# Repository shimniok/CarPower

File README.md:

CarPower
========

Automotive grade 5V power supply. Design to handle automotive electrical system spikes, wide temperature ranges.

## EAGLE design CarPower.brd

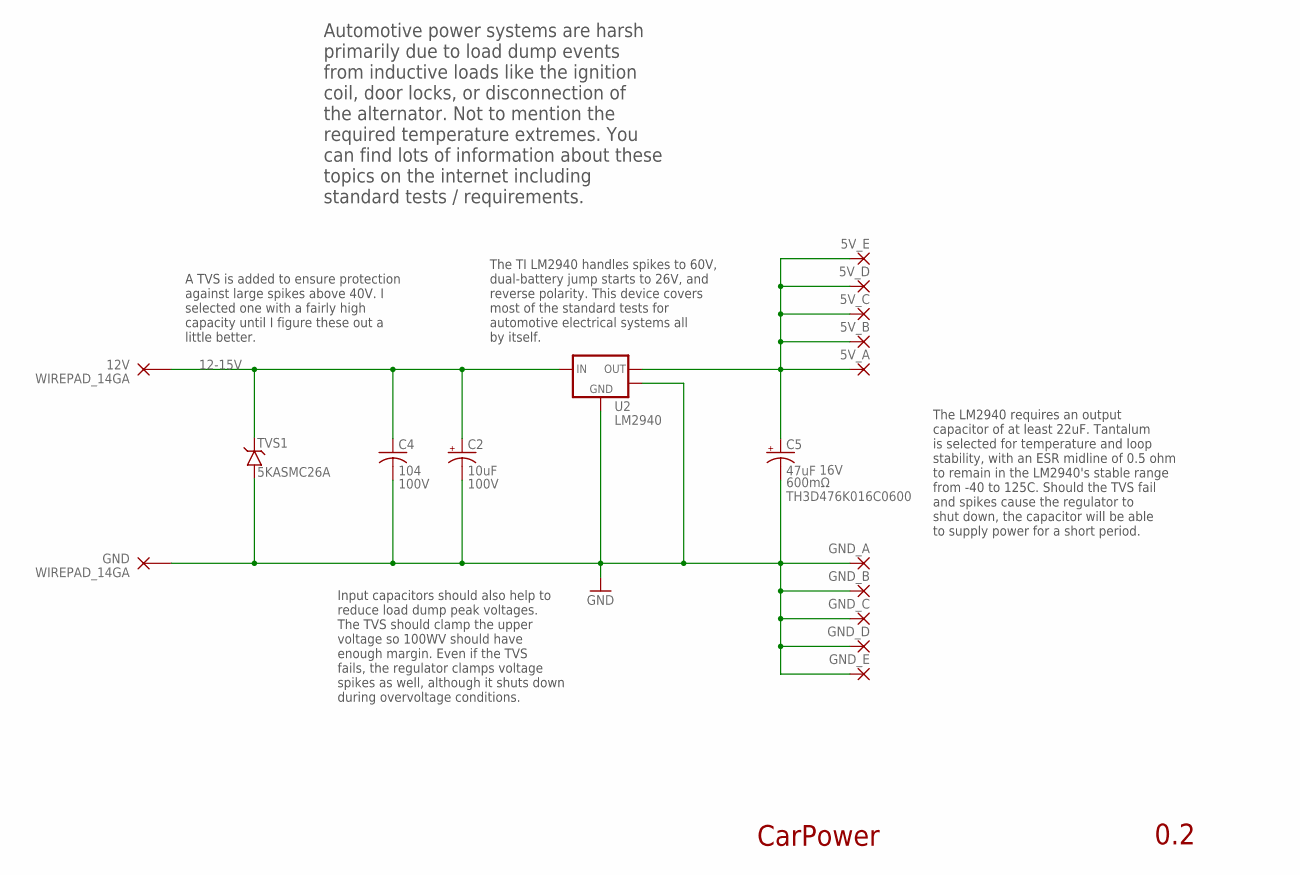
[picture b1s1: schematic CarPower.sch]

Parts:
5V_A, 5V_B, 5V_C, 5V_D, 5V_E: 1,6/0,9
12V: WIREPAD_14GA; PAD_14GA
C2: 10uF; E3,5-8; VOLTAGE 100V
C4: 104; C025-024X044; VOLTAGE 100V
C5: 47uF; SMC_C; VOLTAGE 16V; PARTNO TH3D476K016C0600
GND: WIREPAD_14GA; PAD_14GA
GND_A: 1,6/0,9
GND_B: 1,6/0,9
GND_C: 1,6/0,9
GND_D: 1,6/0,9
GND_E: 1,6/0,9
TVS1: 5KASMC26A; DO-214AB
U2: LM2940; TO263-3

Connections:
5V: 5V_A.1, 5V_B.1, 5V_C.1, 5V_D.1, 5V_E.1, C5.+, U2.3 (VOUT)
12-15V: 12V.P$1, C2.+, C4.1, TVS1.C, U2.1 (VIN)
GND: C2.-, C4.2, C5.-, GND.P$1, GND_A.1, GND_B.1, GND_C.1, GND_D.1, GND_E.1, TVS1.A, U2.2 (GND), U2.4 (TAB)

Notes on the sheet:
The TI LM2940 handles spikes to 60V, dual-battery jump starts to 26V, and reverse polarity. This device covers most of the standard tests for automotive electrical systems all by itself.
CarPower
0.2
A TVS is added to ensure protection against large spikes above 40V. I selected one with a fairly high capacity until I figure these out a little better.
The LM2940 requires an output capacitor of at least 22uF. Tantalum is selected for temperature and loop stability, with an ESR midline of 0.5 ohm to remain in the LM2940's stable range from -40 to 125C. Should the TVS fail and spikes cause the regulator to shut down, the capacitor will be able to s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
Automotive power systems are harsh primarily due to load dump events from inductive loads like the ignition coil, door locks, or disconnection of the alternator. Not to mention the required temperature extremes. You can find lots of information about these topics on the internet including standard 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
Input capacitors should also help to reduce load dump peak voltages. The TVS should clamp the upper voltage so 100WV should have enough margin. Even if the TVS fails, the regulator clamps voltage spikes as well, although it shuts down during overvoltage conditions.

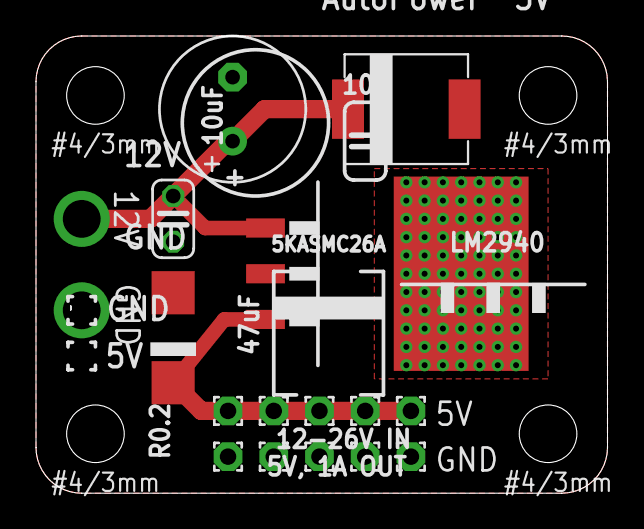
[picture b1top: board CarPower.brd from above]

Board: 2 copper layers, 31.8 x 25.4 mm, 21 parts (0 on the bottom side), 3 nets.

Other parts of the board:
U$1, U$2, U$3, U$4: MOUNT_HOLE_3MM

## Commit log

2014-11-18 Readme
2014-11-18 gitignore
2014-11-18 initial revision
2014-11-18 silkscreen
2014-11-18 gerbers
2014-11-18 updated zip

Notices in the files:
CarPower.brd:
CC-BY-SA
